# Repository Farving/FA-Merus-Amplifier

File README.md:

# FA-Merus-Amplifier
Farving Acoustic Merus Amplifier /w FA-Core interface

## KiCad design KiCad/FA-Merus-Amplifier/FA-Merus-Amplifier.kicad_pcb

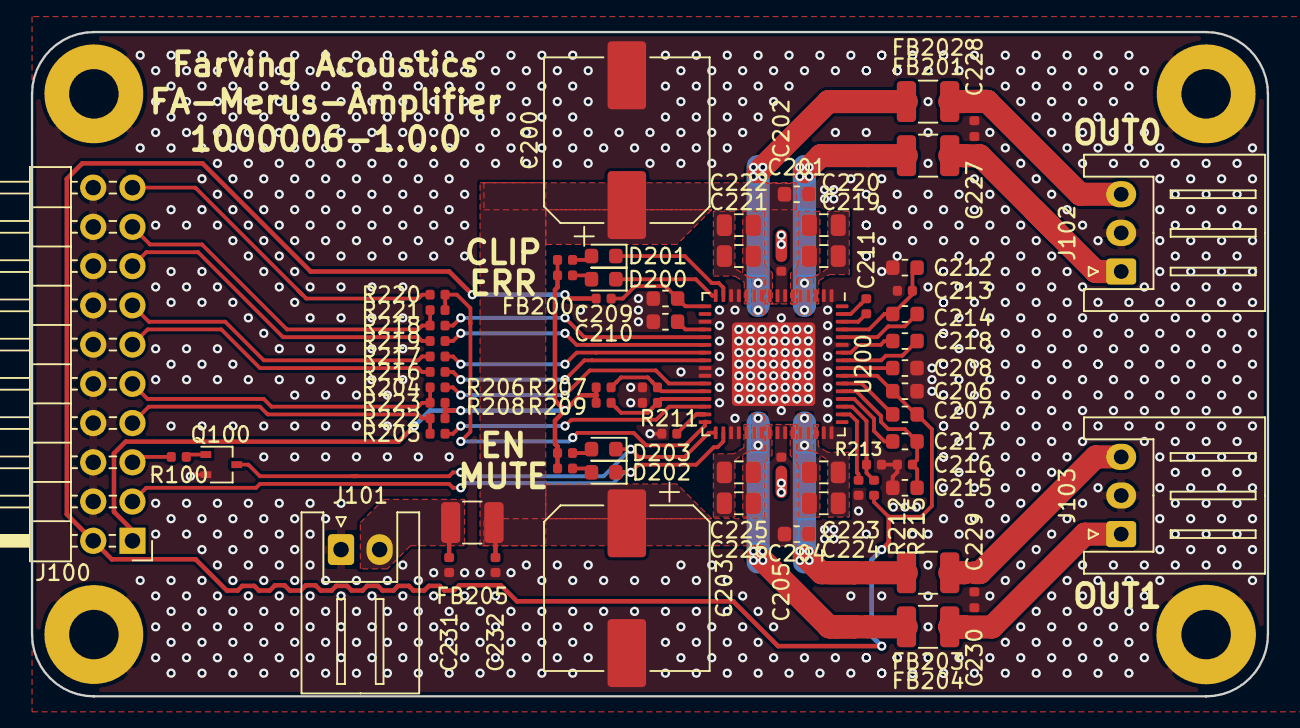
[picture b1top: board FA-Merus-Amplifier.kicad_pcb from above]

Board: 2 copper layers, 80.0 x 43.0 mm, 73 parts (0 on the bottom side), 62 nets.

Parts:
C200, C203: 470u; CP_Elec_10x12.5
C201, C204, C206, C207, C208, C209, C210, C212, C214, C215, C217, C218: 1u; C_0603_1608Metric
C202, C205, C211, C213, C216: 100n; C_0402_1005Metric
C219, C220, C221, C222, C223, C224, C225, C226: 10u; C_0805_2012Metric
C227, C228, C229, C230: 1n; C_0402_1005Metric
C231, C232: 22n; C_0402_1005Metric
D200: Red; LED_0603_1608Metric
D201, D202: Yellow; LED_0603_1608Metric
D203: Green; LED_0603_1608Metric
FB200: 600R; L_0402_1005Metric
FB201, FB202, FB203, FB204, FB205: BLE32PN300SN1L; L_1210_3225Metric
J100: Conn_02x10_Odd_Even; PinHeader_2x10_P2.54mm_Horizontal
J101: JST_XH_S2B-XH-A; JST_XH_S2B-XH-A_1x02_P2.50mm_Horizontal
J102, J103: JST_XH_S3B-XH-A; JST_XH_S3B-XH-A_1x03_P2.50mm_Horizontal
PCB100: 70x43; PCB_Board_70x43
Q100: BC846BW; SOT-323_SC-70
R100: 10k; R_0402_1005Metric
R200, R201, R202, R203, R204, R205: 100R; R_0402_1005Metric
R206, R207, R208, R209, R211, R212, R213, R215, R216, R217, R218, R219, R220, R221: 0R; R_0402_1005Metric
R222, R223: 2.2k; R_0402_1005Metric
U200: MA120x0P; QFN-64-1EP_9x9mm_P0.5mm_EP5.4x5.4mm

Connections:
+3V3: J100.1, R200.1, R201.1, R202.1, R203.1, R206.1, R208.1, R222.1, R223.1
+5V: C206.2, C207.2, FB200.2, J100.2, R212.1, U200.55
/ENABLE: J100.5, R100.2
/I2C_SCL: J100.9, R204.2, R223.2
/I2C_SDA: J100.7, R205.2, R222.2
/I2S_BCLK: J100.17, R218.2, R221.2
/I2S_LRCLK: J100.15, R219.2
/I2S_MCLK: J100.19, R220.2
/I2S_SD0: J100.13, R217.2
/I2S_SD1: J100.11, R216.2
/MA120x0P/AVDD: C209.1, FB200.1, U200.17
/MA120x0P/OUT0A: C227.1, FB201.1, J102.1
/MA120x0P/OUT0B: C228.2, FB202.1, J102.3
/MA120x0P/OUT1A: C229.1, FB203.1, J103.3
/MA120x0P/OUT1B: C230.2, FB204.1, J103.1
/MA120x0P/nCLIP: D201.1, U200.15
/MA120x0P/nENABLE: D203.1, Q100.3, U200.33
/MA120x0P/nERROR: D200.1, U200.16
/VIN: C231.1, FB205.1, J101.2
/nMUTE: D202.1, J100.3, U200.34
AVSS: C200.2, C201.2, C202.2, C203.2, C204.2, C205.2, C206.1, C208.2, C209.2, C210.2, C212.2, C213.2, C215.1, C216.1, C227.2, C228.1, C229.2, C230.1, C231.2, C232.2, J100.4, J100.6, J100.8, J100.10, J100.12, J100.14, J100.16, J100.18, J100.20, J101.1, J102.2, J103.2, PCB100.1, PCB100.2, PCB100.3, PCB100.4, Q100.2, R207.2, R209.2, R211.2, R213.2, R215.2, U200.1, U200.2, U200.13, U200.14, U200.19, U200.25, U200.26, U200.35, U200.36, U200.47, U200.48, U200.59, U200.65
unnamed: C207.1, U200.54
unnamed: C208.1, U200.56
unnamed: C210.1, U200.20
unnamed: C211.1, U200.63
unnamed: C211.2, U200.62
unnamed: C212.1, C213.1, C214.1, U200.61
unnamed: C214.2, U200.60
unnamed: C215.2, C216.2, C217.2, U200.53
unnamed: C217.1, U200.52
unnamed: C218.1, U200.58
unnamed: C218.2, U200.57
unnamed: C219.1, C220.1, U200.6
unnamed: C219.2, C220.2, U200.3
unnamed: C221.1, C222.1, U200.9
unnamed: C221.2, C222.2, U200.12
unnamed: C223.1, C224.1, U200.43
unnamed: C223.2, C224.2, U200.46
unnamed: C225.1, C226.1, U200.37
unnamed: C225.2, C226.2, U200.40
unnamed: D200.2, R200.2
unnamed: D201.2, R201.2
unnamed: D202.2, R202.2
unnamed: D203.2, R203.2
unnamed: FB201.2, U200.4, U200.5
unnamed: FB202.2, U200.10, U200.11
unnamed: FB203.2, U200.44, U200.45
unnamed: FB204.2, U200.38, U200.39
unnamed: Q100.1, R100.1
unnamed: R204.1, U200.27
unnamed: R205.1, U200.30
unnamed: R206.2, R207.1, U200.28
unnamed: R208.2, R209.1, U200.29
unnamed: R211.1, U200.31
unnamed: R212.2, R213.1, U200.51
unnamed: R215.1, U200.50
unnamed: R216.1, U200.24
unnamed: R217.1, U200.23
unnamed: R218.1, U200.21
unnamed: R219.1, U200.22
unnamed: R220.1, R221.1, U200.32
PVDD: C200.1, C201.1, C202.1, C203.1, C204.1, C205.1, C232.1, FB205.2, U200.7, U200.8, U200.41, U200.42

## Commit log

2020-06-30 Staged Project
2020-07-06 RC-1.0.0
2020-11-10 Update for release
